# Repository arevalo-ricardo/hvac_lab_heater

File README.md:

# THRM-SYNC (`thrm-sync-pcb`)

Custom multi-channel PWM heater driver and telemetry PCB designed for HVAC thermal synchronization experiments.

---

## Overview
**THRM-SYNC** regulates resistive heating loads using 5V logic-level PWM switching and provides real-time telemetry over I2C. It is built for benchtop HVAC lab testing to study heat transfer, thermal mass behavior, and multi-zone synchronization.

---

## Hardware Specifications

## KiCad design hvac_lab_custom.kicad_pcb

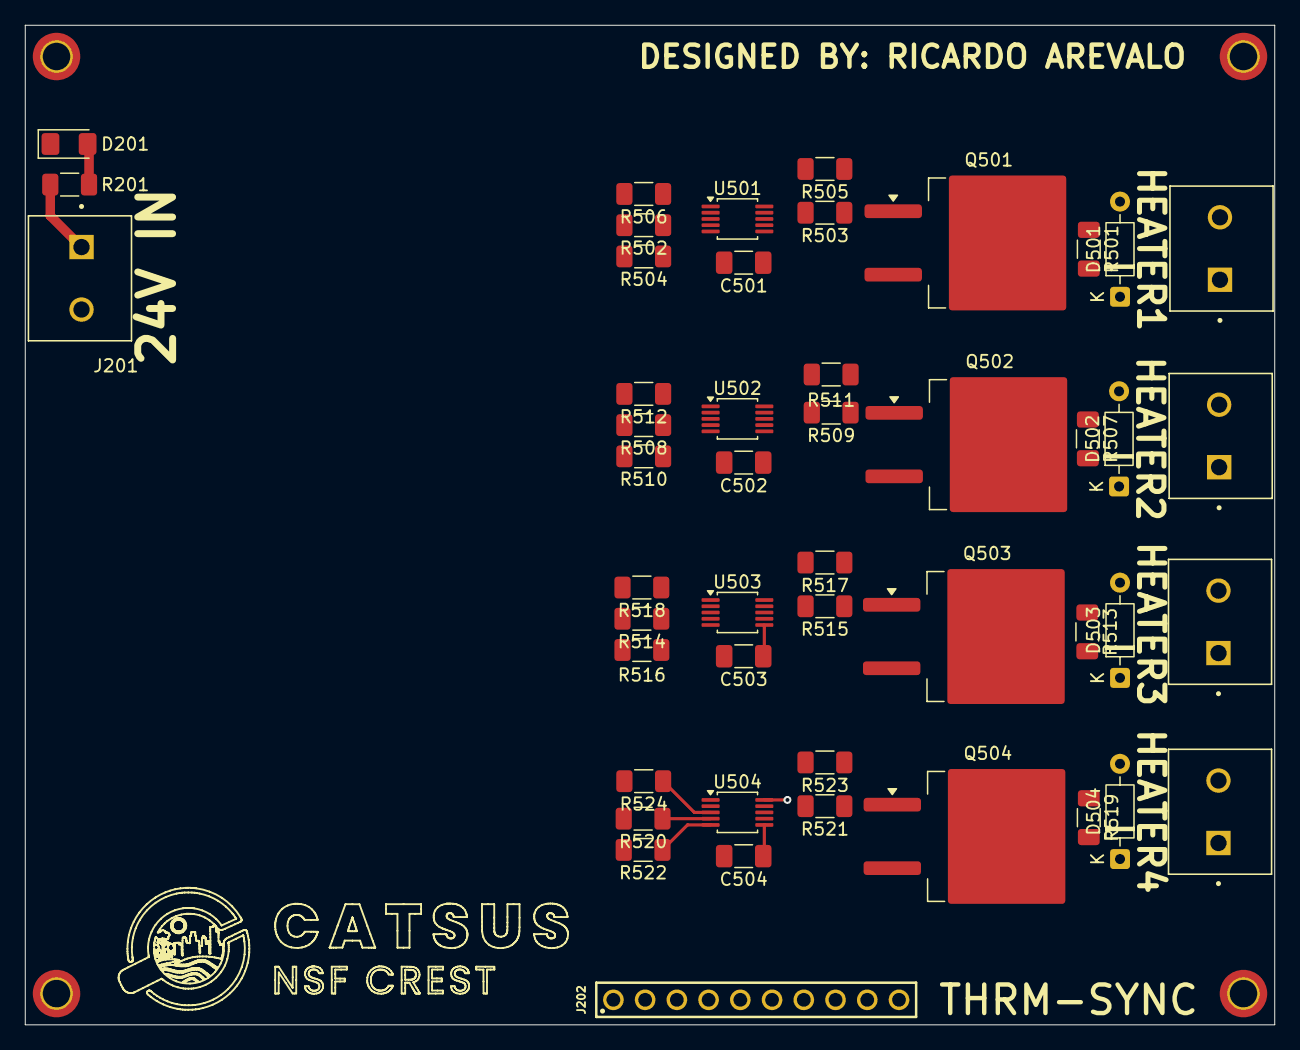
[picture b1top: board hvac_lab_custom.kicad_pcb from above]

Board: 4 copper layers, 100.0 x 80.0 mm, 48 parts (0 on the bottom side), 23 nets.

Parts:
C501, C502, C503, C504: 100nF; C_1206_3216Metric_Pad1.33x1.80mm_HandSolder
D201: STATUS_LED; LED_1206_3216Metric_Pad1.42x1.75mm_HandSolder
D501, D502, D503, D504: 1N914; D_DO-35_SOD27_P7.62mm_Horizontal
J201, J501, J502, J503, J504: 1935161; PHOENIX_1935161
J202: 6130XX11121_61301011121; 61301011121
Q501, Q502, Q503, Q504: IRFZ44NSTRLPBF; TO-263-2
R201: 12k; R_1206_3216Metric_Pad1.30x1.75mm_HandSolder
R501, R507, R513, R519: 0.01; R_1206_3216Metric_Pad1.30x1.75mm_HandSolder
R502, R504, R505, R506, R508, R510, R511, R512, R514, R516, R517, R518, R520, R522, R523, R524: 10k; R_1206_3216Metric_Pad1.30x1.75mm_HandSolder
R503, R509, R515, R521: 100; R_1206_3216Metric_Pad1.30x1.75mm_HandSolder
U501, U502, U503, U504: INA238; TSSOP-10_3x3mm_P0.5mm

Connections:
+24V: J201.1, R201.2, R501.1, R507.1, R513.1, R519.1, U501.8 (Vbus), U501.10 (Vin+), U502.8 (Vbus), U502.10 (Vin+), U503.8 (Vbus), U503.10 (Vin+), U504.8 (Vbus), U504.10 (Vin+)
GND: C501.2, C502.2, C503.2, C504.2, D201.1 (K), J201.2, J202.10, Q501.3 (S), Q502.3 (S), Q503.3 (S), Q504.3 (S), R505.1, R511.1, R517.1, R523.1, U501.1 (A1), U501.2 (A0), U501.7 (GND), U502.1 (A1), U502.7 (GND), U503.2 (A0), U503.7 (GND), U504.7 (GND)
I2C0_SCL: J202.7, R502.1, R508.1, R514.1, R520.1, U501.4 (SDA), U502.4 (SDA), U503.4 (SDA), U504.4 (SDA)
I2C0_SDA: J202.8, R504.1, R510.1, R516.1, R522.1, U501.5 (SCL), U502.5 (SCL), U503.5 (SCL), U504.5 (SCL)
MCU_VCC: C501.1, C502.1, C503.1, C504.1, J202.1, R502.2, R504.2, R506.2, R508.2, R510.2, R512.2, R514.2, R516.2, R518.2, R520.2, R522.2, R524.2, U501.6 (VS), U502.2 (A0), U502.6 (VS), U503.1 (A1), U503.6 (VS), U504.1 (A1), U504.2 (A0), U504.6 (VS)
unnamed: D201.2 (A), R201.1
unnamed: D501.2 (A), J501.2, Q501.2 (D)
unnamed: D501.1 (K), J501.1, R501.2, U501.9 (Vin-)
unnamed: D502.2 (A), J502.2, Q502.2 (D)
unnamed: D502.1 (K), J502.1, R507.2, U502.9 (Vin-)
unnamed: D503.2 (A), J503.2, Q503.2 (D)
unnamed: D503.1 (K), J503.1, R513.2, U503.9 (Vin-)
unnamed: D504.2 (A), J504.2, Q504.2 (D)
unnamed: D504.1 (K), J504.1, R519.2, U504.9 (Vin-)
unnamed: Q501.1 (G), R503.1
unnamed: Q502.1 (G), R509.1
unnamed: Q503.1 (G), R515.1
unnamed: Q504.1 (G), R521.1
PWM1: J202.2, R503.2, R505.2
PWM2: J202.3, R509.2, R511.2
PWM3: J202.4, R515.2, R517.2
PWM4: J202.5, R521.2, R523.2
~ALERT: J202.9, R506.1, R512.1, R518.1, R524.1, U501.3 (~Alert), U502.3 (~Alert), U503.3 (~Alert), U504.3 (~Alert)
